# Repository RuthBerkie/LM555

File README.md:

# LM555

This schematic design is an adjustable LED flasher circuit configured as an astable multivibrator using the classic 555 timer IC. It automatically generates a continuous stream of square-wave pulses, causing the green LED to blink repeatedly at a speed (frequency) that can manually be tuned.

Component Breakdown & Functions

Core Integrated Circuit

• U1 (LM555xN): The main 555 timer IC. It acts as an electronic oscillator that continuously switches its output pin between HIGH (+5V) and LOW (0V) states.
    
    • Pin 1 — GND (Ground): This serves as the universal reference point (0V) for the entire circuit. It connects directly to the negative terminal of your power supply to complete the electrical circuit loop.

    • Pin 2 — TRIG (Trigger): This acts as the "Turn On" switch for the chip's output. Whenever the electrical voltage on this specific pin drops below 1/3 of your main power supply voltage, it forces the chip's primary output (Pin 3) to flip into a HIGH state.
  
    • Pin 3 — OUT (Output): This is the power driver where the chip delivers its finalized timing signal. It is robust enough to push or pull up to 200mA of electric current, making it ideal for directly powering external components like flashing LEDs, audible buzzers, or switching relays.

    • Pin 4 — RESET (Reset): This functions as a master system override. Applying a LOW voltage (0V) to this pin immediately cuts off the system and forces the output (Pin 3) to turn off. In regular circuit configurations, it is tied directly to the positive power supply (+VCC) so the chip doesn’t experience accidental resets from stray static.

    • Pin 5 — CONT (Control Voltage): This behaves as a threshold tuner by giving you external access to the internal voltage divider network. In standard projects, designers attach a tiny capacitor here to isolate the chip from external electrical noise and keep the overall timing steady.

    • Pin 6 — THRES (Threshold): This serves as the "Turn Off" switch for the output. When the voltage charging up on this pin rises past 2/3 of your main power supply voltage, it trips the internal mechanics and forces the output (Pin 3) to flip LOW, successfully ending that specific pulse cycle.

    • Pin 7 — DISCH (Discharge): This is the dedicated capacitor drain. Internally, it is connected to a microscopic transistor switch. When the main output flips to a LOW state, this pin activates a direct connection to GND, allowing your timing capacitor an easy path to empty its stored energy.

    • Pin 8 — VCC (Voltage Common Collector): This is the main power input for the integrated circuit. It connects directly to the positive terminal of your power supply. For standard 555 models, it safely accepts a wide power range, typically anywhere from +4.5V up to +16V.

 • Pins 2 and 6 are tied together: This forces the chip to continuously watch its own timing capacitor. As the capacitor charges up past the Threshold (Pin 6) limit, the chip shuts off the output. As the capacitor drains down past the Trigger (Pin 2) limit, the chip turns the output back on.
 
 • Pin 7 manages the timing speed: It opens and closes the drainage path, causing the capacitor to cycle up and down based on the resistance of your potentiometer.

Power & Support Elements

    • J1 (Screw_Terminal_01x02): A 2-pin terminal block. It serves as the main power input connection point to hook up an external 5V power supply and ground.
    • C1 (100n): A 100nF ceramic decoupling capacitor. It sits across the power rails to filter out high-frequency electrical noise and stabilize the incoming 5V supply.
    • C2 (10n): A 10nF bypass capacitor connected to the Control Voltage pin (Pin 5). It prevents stray electrical noise from interfering with the internal voltage references of the timer.
    • H1, H2, H3, H4 (MountingHole_Pad): Mechanical mounting holes for securing the physical circuit board with screws. They are connected to GND to provide a clean grounding path or shielding.

Timing Network (Frequency Control)

    • C3 (47u/16v): A 47µF polarized electrolytic timing capacitor. This component continuously charges and discharges to dictate the time duration of the ON and OFF states.
    • The Upper Threshold (2/3 of VCC): 3.33V. When the timing capacitor C3 charges up from zero and hits this exact voltage, Pin 6 (Threshold) triggers the 555 chip to turn the green LED OFF and begin discharging.
    • The Lower Trigger (1/3 of VCC): 1.67V. As the capacitor C3 empties its energy into Pin 7, the voltage drops. The moment it falls to this exact voltage, Pin 2 (Trigger) trips the chip to turn the green LED back ON and start the charging cycle all over again.
    
    In short, your capacitor C3 will continuously bounce back and forth between 1.67V and 3.33V forever while the circuit is powered.

    • R1 (1k): A 1kΩ fixed resistor. It controls the charging rate and prevents a direct short-circuit between the +5V power supply and ground when the IC activates its internal discharge pin (Pin 7).
    • R2 (1k): A 1kΩ fixed resistor. It sets a minimum safety baseline resistance for the timing network so that even if the potentiometer is dialed down to zero, the circuit won't malfunction.
    • RV1 (10k): A 10kΩ variable resistor (potentiometer). Turning this dial changes the overall resistance of the timing path, allowing you to speed up or slow down how fast C3 charges and discharges, which changes the LED blink rate.

 How the Circuit Works

    1. The Charging Phase: Current flows from +5V through R1, R2, and RV1 to charge the capacitor C3. While it charges, the output (Pin 3) stays HIGH (+5V), turning the green LED ON.
    2. The Threshold Trigger: Once the voltage across C3 reaches 2/3 of the supply voltage, the 555 timer trips internally. The output (Pin 3) flips to LOW (0V), turning the green LED OFF, and Pin 7 internally connects to ground.
    3. The Discharging Phase: The energy stored in C3 begins draining backward through RV1 and R2 directly into the discharge pin (Pin 7).
    4. The Reset Trigger: As soon as the voltage across C3 drops down to 1/3 of the supply voltage, the timer trips again. Pin 7 closes its connection to ground, the output goes back to HIGH, the LED turns ON, and the loop starts all over again.

Output Elements

    • R3 (1k): A 1kΩ current-limiting resistor. It protects the LED from receiving too much current from the output pin (Pin 3), preventing it from burning out.
    • D1 (Green): A green Light Emitting Diode. It flashes on and off visually to show the output pulses generated by the 555 timer.

This is a two-layer Printed Circuit Board (PCB) layout.

Key Features of the Design

    • Dual-Layer Copper Fill: The entire background of the board (the large shaded red/purple area) is a GND (Ground) Copper Pour applied to both the front layer (F.Cu) and back layer (B.Cu), as configured in the first image's properties window. This massive ground plane acts as a shield against electrical noise and simplifies routing.

    • Component Arrangement: The 555 timer chip (U1) sits at the center, flanked by its timing resistors (R1, R2) and potentiometer (RV1) along the top. The power input terminal (J1) is placed on the right, while the output indicator LED (D1) sits at the bottom left.

    • Trace Routing: Red lines represent physical copper traces on the front side of the board that carry signals and 5V power between the component pins.

    • GND-Bonded Mounting Holes: The four large mounting holes in the corners are explicitly tied directly to the GND plane. When you screw this board down into a metal chassis, it automatically grounds the chassis for electrical safety.
    
    • Thermal Reliefs: As seen in the settings image, pads connecting to the massive GND plane use a "thermal relief" pattern (small cross-spokes instead of solid copper). This prevents heat from escaping too fast during soldering, making it much easier to solder components like the capacitors and mounting holes.

FINAL RESULT

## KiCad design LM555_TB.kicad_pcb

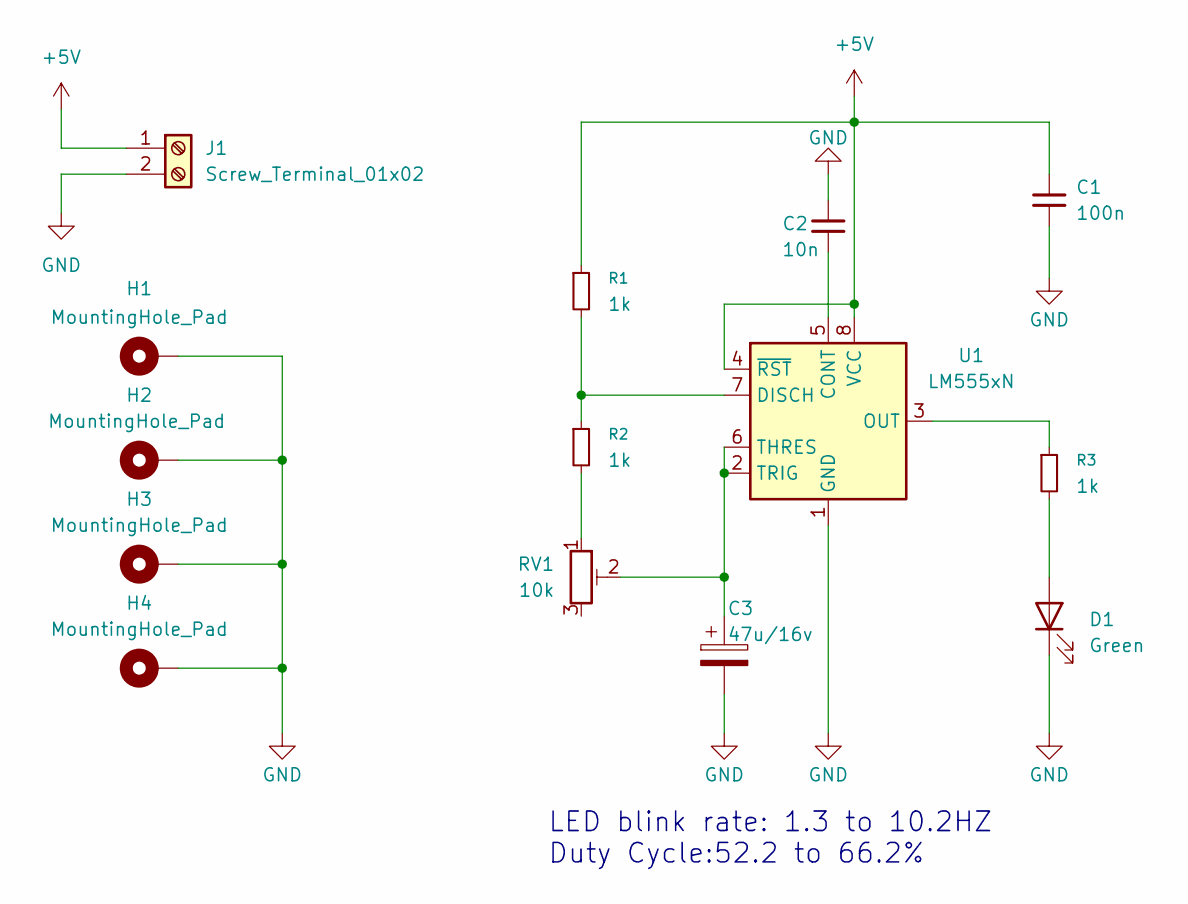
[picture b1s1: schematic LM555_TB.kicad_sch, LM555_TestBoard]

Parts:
C1: 100n; C_Disc_D7.0mm_W2.5mm_P5.00mm
C2: 10n; C_Disc_D7.0mm_W2.5mm_P5.00mm
C3: 47u/16v; CP_Radial_D5.0mm_P2.50mm
D1: Green; LED_D3.0mm
H1, H2, H3, H4: MountingHole_Pad; MountingHole_3.2mm_M3_DIN965_Pad
J1: Screw_Terminal_01x02; TerminalBlock_Phoenix_PT-1,5-2-3.5-H_1x02_P3.50mm_Horizontal
R1, R2, R3: 1k; R_Axial_DIN0207_L6.3mm_D2.5mm_P10.16mm_Horizontal
RV1: 10k; Potentiometer_Bourns_3386P_Vertical
U1: LM555xN; DIP-8_W7.62mm

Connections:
+5V: C1.1, J1.1, R1.1, U1.4 (~RST), U1.8 (VCC)
GND: C1.2, C2.1, C3.2, D1.1 (K), H1.1 (1_1), H2.1 (1_1), H3.1 (1_1), H4.1 (1_1), J1.2, U1.1 (GND)
unnamed: D1.2 (A), R3.2
unnamed: R2.2, RV1.1
unnamed: C2.2, U1.5 (CONT)
unnamed: R1.2, R2.1, U1.7 (DISCH)
unnamed: R3.1, U1.3 (OUT)
unnamed: C3.1, RV1.2, U1.2 (TRIG), U1.6 (THRES)

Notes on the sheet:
LED blink rate: 1.3 to 10.2HZ Duty Cycle:52.2 to 66.2%

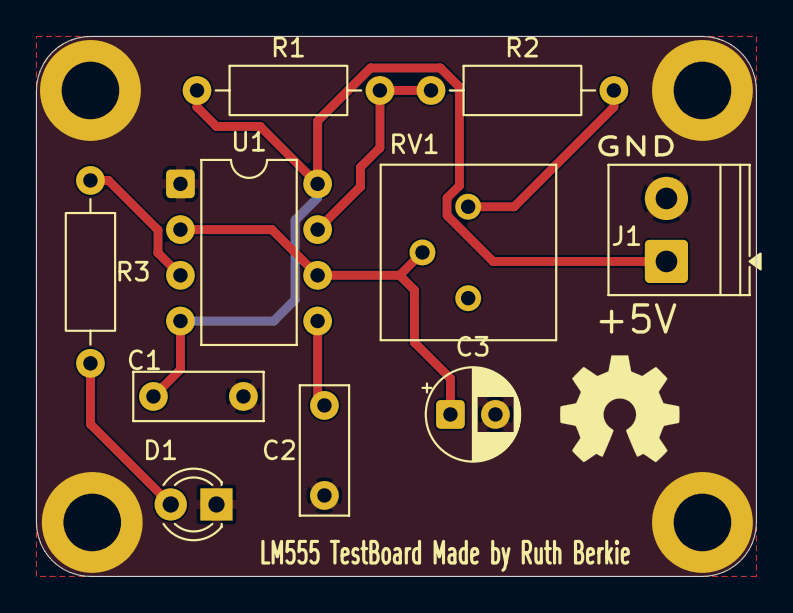
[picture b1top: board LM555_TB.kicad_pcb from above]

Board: 2 copper layers, 40.0 x 30.0 mm, 14 parts (0 on the bottom side), 8 nets.
